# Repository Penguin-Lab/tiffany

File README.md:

# tiffany
A Tiffany é uma hexapod desenvolvida para andar de forma autônoma ou para ser controlada pelo celular. Para se locomover, ela possui 6 patas de 3 graus de liberdade cada (3 motores) e uma ESP32 que comanda o conjunto! Ela é a segunda integrante robótica do nosso espaço inteligente!

# Estrutura física
A estrutura física do robô é composta por seis patas de três eixos cada (três motores). As patas são fixadas a duas placas de PLA para deixar o robô firme. As peças são todas projetadas em 3D e foram impressas utilizando PLA, podendo ser encontradas na pasta Pecas_3d deste projeto.

## Peças 3D em STL
As peças em 3D desenvolvidas para este projeto foram baseadas no projeto do hexapod Steve da Eng. Eletricista Bruna Reis Lyra. Na pasta Pecas_3d, é possível encontrar duas versões dessas peças em STL: uma desenhada para o motor servo TowerPro MG995 (v1) e outra para o DS3230 (v2). Para ajudar, segue abaixo uma lista de todas as peças que devem ser impressas e qual o valor da sua maior dimensão (para ajudar na escolha da impressora):

### V1: Versão para o motor servo TowerPro MG995 
* Corpo
  * 1x [TIFFANY_BODY_DOWN.STL (230 mm)](https://github.com/Penguin-Lab/tiffany/blob/main/Pecas_3d/v1/TIFFANY_BODY_DOWN.STL)
  * 1x [TIFFANY_BODY_UP.STL (230 mm)](https://github.com/Penguin-Lab/tiffany/blob/main/Pecas_3d/v1/TIFFANY_BODY_UP.STL)
  * 6x [TIFFANY_SPACER.STL (68 mm)](https://github.com/Penguin-Lab/tiffany/blob/main/Pecas_3d/v1/TIFFANY_SPACER.STL)
  * 1x [TIFFANY_SUPPORT_PCI.STL (120 mm)](https://github.com/Penguin-Lab/tiffany/blob/main/Pecas_3d/v1/TIFFANY_SUPPORT_PCI.STL)
  * 1x [TIFFANY_SUPPORT_SWITCH.STL (50 mm)](https://github.com/Penguin-Lab/tiffany/blob/main/Pecas_3d/v1/TIFFANY_SUPPORT_SWITCH.STL)
* Patas
  * 6x [TIFFANY_TIBIA_LEFT.STL (141 mm)](https://github.com/Penguin-Lab/tiffany/blob/main/Pecas_3d/v1/TIFFANY_TIBIA_LEFT.STL)
  * 6x [TIFFANY_TIBIA_LEFT.STL espelhado (141 mm)](https://github.com/Penguin-Lab/tiffany/blob/main/Pecas_3d/v1/TIFFANY_TIBIA_LEFT.STL)
  * 6x [TIFFANY_TIBIA_MIDDLE.STL (63 mm)](https://github.com/Penguin-Lab/tiffany/blob/main/Pecas_3d/v1/TIFFANY_TIBIA_MIDDLE.STL)
  * 6x [TIFFANY_TIBIA_TUBO.STL (10 mm)](https://github.com/Penguin-Lab/tiffany/blob/main/Pecas_3d/v1/TIFFANY_TIBIA_TUBO.STL)
  * 6x [TIFFANY_FOOT.STL (25 mm)](https://github.com/Penguin-Lab/tiffany/blob/main/Pecas_3d/v1/TIFFANY_FOOT.STL)
  * 3x [TIFFANY_FEMUR_FRONT.STL (110 mm)](https://github.com/Penguin-Lab/tiffany/blob/main/Pecas_3d/v1/TIFFANY_FEMUR_FRONT.STL)
  * 3x [TIFFANY_FEMUR_BACK.STL (118 mm)](https://github.com/Penguin-Lab/tiffany/blob/main/Pecas_3d/v1/TIFFANY_FEMUR_BACK.STL)
  * 3x [TIFFANY_FEMUR_FRONT.STL espelhado (110 mm)](https://github.com/Penguin-Lab/tiffany/blob/main/Pecas_3d/v1/TIFFANY_FEMUR_FRONT.STL)
  * 3x [TIFFANY_FEMUR_BACK.STL espelhado (118 mm)](https://github.com/Penguin-Lab/tiffany/blob/main/Pecas_3d/v1/TIFFANY_FEMUR_BACK.STL)
  * 6x [TIFFANY_FEMUR_MIDDLE.STL (51 mm)](https://github.com/Penguin-Lab/tiffany/blob/main/Pecas_3d/v1/TIFFANY_FEMUR_MIDDLE.STL)
  * 6x [TIFFANY_OMBRO_UP.STL (61 mm)](https://github.com/Penguin-Lab/tiffany/blob/main/Pecas_3d/v1/TIFFANY_OMBRO_UP.STL)
  * 3x [TIFFANY_OMBRO_DOWN_LEFT.STL (61 mm)](https://github.com/Penguin-Lab/tiffany/blob/main/Pecas_3d/v1/TIFFANY_OMBRO_DOWN_LEFT.STL)
  * 3x [TIFFANY_OMBRO_DOWN_LEFT.STL espelhado (61 mm)](https://github.com/Penguin-Lab/tiffany/blob/main/Pecas_3d/v1/TIFFANY_OMBRO_DOWN_LEFT.STL)
* Motor
  * 12x [TIFFANY_TAMPA_MOTOR.STL (41 mm)](https://github.com/Penguin-Lab/tiffany/blob/main/Pecas_3d/v1/TIFFANY_TAMPA_MOTOR.STL)

Obs: a tampa de 12 motores deverão ser trocadas pelas peças [TIFFANY_TAMPA_MOTOR.STL](https://github.com/Penguin-Lab/tiffany/blob/main/Pecas_3d/v1/TIFFANY_TAMPA_MOTOR.STL) para que seja possível fixar os rolamentos nas patas. Serão utilizados 3 rolamentos por pata:

### V2: Versão para o motor servo DS3230 PRO-180 
* Corpo
  * 1x [TIFFANY_BODY_DOWN.STL (230 mm)](https://github.com/Penguin-Lab/tiffany/blob/main/Pecas_3d/v2/TIFFANY_BODY_DOWN.STL)
  * 1x [TIFFANY_BODY_UP.STL (230 mm)](https://github.com/Penguin-Lab/tiffany/blob/main/Pecas_3d/v2/TIFFANY_BODY_UP.STL)
  * 2x [TIFFANY_SPACER.STL (67 mm)](https://github.com/Penguin-Lab/tiffany/blob/main/Pecas_3d/v2/TIFFANY_SPACER.STL)
  * 4x [TIFFANY_SPACER_FRONT.STL (63 mm)](https://github.com/Penguin-Lab/tiffany/blob/main/Pecas_3d/v2/TIFFANY_SPACER_FRONT.STL)
  * 1x [TIFFANY_SUPORT_PCI.STL (120 mm)](https://github.com/Penguin-Lab/tiffany/blob/main/Pecas_3d/v2/TIFFANY_SUPORT_PCI.STL)
  * 1x [TIFFANY_SUPORT_SWITCH.STL (50 mm)](https://github.com/Penguin-Lab/tiffany/blob/main/Pecas_3d/v2/TIFFANY_SUPORT_SWITCH.STL)
  * 1x [TIFFANY_SUPORT_BATTERY_PLUG.STL (44 mm)](https://github.com/Penguin-Lab/tiffany/blob/main/Pecas_3d/v2/TIFFANY_SUPORT_BATTERY_PLUG.STL)
  * 1x [TIFFANY_LOGO.STL (36 mm)](https://github.com/Penguin-Lab/tiffany/blob/main/Pecas_3d/v2/TIFFANY_LOGO.STL)
* Patas
  * 6x [TIFFANY_TIBIA_LEFT.STL (141 mm)](https://github.com/Penguin-Lab/tiffany/blob/main/Pecas_3d/v2/TIFFANY_TIBIA_LEFT.STL)
  * 6x [TIFFANY_TIBIA_LEFT.STL espelhado (141 mm)](https://github.com/Penguin-Lab/tiffany/blob/main/Pecas_3d/v2/TIFFANY_TIBIA_LEFT.STL)
  * 6x [TIFFANY_TIBIA_MIDDLE.STL (63 mm)](https://github.com/Penguin-Lab/tiffany/blob/main/Pecas_3d/v2/TIFFANY_TIBIA_MIDDLE.STL)
  * 6x [TIFFANY_TIBIA_TUBO.STL (10 mm)](https://github.com/Penguin-Lab/tiffany/blob/main/Pecas_3d/v2/TIFFANY_TIBIA_TUBO.STL)
  * 6x [TIFFANY_FOOT.STL (25 mm)](https://github.com/Penguin-Lab/tiffany/blob/main/Pecas_3d/v2/TIFFANY_FOOT.STL)
  * 3x [TIFFANY_FEMUR_FRONT.STL (110 mm)](https://github.com/Penguin-Lab/tiffany/blob/main/Pecas_3d/v2/TIFFANY_FEMUR_FRONT.STL)
  * 3x [TIFFANY_FEMUR_BACK.STL (118 mm)](https://github.com/Penguin-Lab/tiffany/blob/main/Pecas_3d/v2/TIFFANY_FEMUR_BACK.STL)
  * 3x [TIFFANY_FEMUR_FRONT.STL espelhado (110 mm)](https://github.com/Penguin-Lab/tiffany/blob/main/Pecas_3d/v2/TIFFANY_FEMUR_FRONT.STL)
  * 3x [TIFFANY_FEMUR_BACK.STL espelhado (118 mm)](https://github.com/Penguin-Lab/tiffany/blob/main/Pecas_3d/v2/TIFFANY_FEMUR_BACK.STL)
  * 6x [TIFFANY_FEMUR_MIDDLE.STL (51 mm)](https://github.com/Penguin-Lab/tiffany/blob/main/Pecas_3d/v2/TIFFANY_FEMUR_MIDDLE.STL)
  * 6x [TIFFANY_OMBRO_UP.STL (61 mm)](https://github.com/Penguin-Lab/tiffany/blob/main/Pecas_3d/v2/TIFFANY_OMBRO_UP.STL)
  * 3x [TIFFANY_OMBRO_DOWN_LEFT.STL (61 mm)](https://github.com/Penguin-Lab/tiffany/blob/main/Pecas_3d/v2/TIFFANY_OMBRO_DOWN_LEFT.STL)
  * 3x [TIFFANY_OMBRO_DOWN_LEFT.STL espelhado (61 mm)](https://github.com/Penguin-Lab/tiffany/blob/main/Pecas_3d/v2/TIFFANY_OMBRO_DOWN_LEFT.STL)
* Motor
  * 12x [TIFFANY_TAMPA_MOTOR_DS3230.STL (41 mm)](https://github.com/Penguin-Lab/tiffany/blob/main/Pecas_3d/v2/TIFFANY_TAMPA_MOTOR_DS3230.STL)

Obs: no caso do DS3230, a tampa de 12 motores deverão ser trocadas pelas peças [TIFFANY_TAMPA_MOTOR_DS3230.STL](https://github.com/Penguin-Lab/tiffany/blob/main/Pecas_3d/v2/TIFFANY_TAMPA_MOTOR_DS3230.STL) para que seja possível fixar os rolamentos nas patas. Serão utilizados 3 rolamentos por pata.

## Outros itens da estrutura
Alguns outros itens são necessários para finalizar a estrutura da Tiffany:
* 6x Parafusos m4 ou similar de cm: prender as peças [TIFFANY_BODY_UP.STL](https://github.com/Penguin-Lab/tiffany/blob/main/Pecas_3d/TIFFANY_BODY_UP.STL) e [TIFFANY_BODY_DOWN.STL](https://github.com/Penguin-Lab/tiffany/blob/main/Pecas_3d/TIFFANY_BODY_DOWN.STL)
* 24x Parafusos m4 de cm: prender as peças [TIFFANY_OMBRO_DOWN_LEFT.STL](https://github.com/Penguin-Lab/tiffany/blob/main/Pecas_3d/TIFFANY_OMBRO_DOWN_LEFT.STL) e [TIFFANY_OMBRO_UP.STL](https://github.com/Penguin-Lab/tiffany/blob/main/Pecas_3d/TIFFANY_OMBRO_UP.STL)
* 24x Parafusos m3 de cm: prender as peças [TIFFANY_TIBIA_LEFT.STL](https://github.com/Penguin-Lab/tiffany/blob/main/Pecas_3d/TIFFANY_TIBIA_LEFT.STL) nos motores
* 6x Tiras de EVA: colocar na ponta das peças [TIFFANY_FOOT.STL](https://github.com/Penguin-Lab/tiffany/blob/main/Pecas_3d/TIFFANY_FOOT.STL) para evitar que o robô deslize
* Arruelas entre as peças [TIFFANY_SPACER.STL](https://github.com/Penguin-Lab/tiffany/blob/main/Pecas_3d/TIFFANY_SPACER.STL) e [TIFFANY_BODY_UP.STL](https://github.com/Penguin-Lab/tiffany/blob/main/Pecas_3d/TIFFANY_BODY_UP.STL) para ajustar a altura correta do interior do robô

## Placa de circuito impresso
No projeto, foi desenvolvida uma placa de circuito para servir como shield para a ESP32 e conexão com as duas placas PCA9685.

## Calibração dos motores
A calibração dos motores é feita utilizando o [CALIBRADOR DE MOTORES](https://github.com/Penguin-Lab/calib_servomotor) conectado às PCAs da Tiffany. Isso deve ser feito pelo clock das PCAs ser diferente de uma placa para outra. Logo, os motores da esquerda são calibrados utilizando a PCA da esquerda e os da direita com a PCA da direita. Os valores retornados pela calibração são jogados nesta [PLANILHA](https://docs.google.com/spreadsheets/d/1Kh9AVbb79lXnJq5dlCiB7NEVVmcJWRX6X2CdDR9_QZo/edit?usp=sharing). A planilha ajeita os valores de PWM retornados na IDE do Arduino para valores que representem 0 e 180 graus dos motores já na estrutura das patas. Esses valores são os mesmos listados no código de comando da Tiffany.

## Componentes eletrônicos
Os componentes eletrônicos embarcados no robô e equipamentos utilizados estão listados abaixo.
### V1: Versão para o motor servo TowerPro MG995 
* Controlador com Wi-fi e Bluetooth
  * 1x ESP32 (38 pinos)
* Motores
  * 18x Servo TowerPro MG995 Metálico
* 2x Placas PCA9685 para comando dos 18 motores (9 motores em cada)
* Chave (switch)
* Alimentação
  * Bateria Zippy LiFe 1100mAh 2s 6,6V (ESP32)
  * Bateria TM Hobbies LiFe 2100mAh 2s 6,6v (motores)

### V2: Versão para o motor servo DS3230 PRO-180 
* Controlador com Wi-fi e Bluetooth
  * 1x ESP32 (38 pinos)
* Motores
  * 18x Servo DS3230 PRO-180
* 2x Placas PCA9685 para comando dos 18 motores (9 motores em cada)
* Chave (switch)
* Chave pequena (switch)
* Alimentação
  * Regulador para 5V (ESP32)
  * Regulador HV SBEC YPG 20A configurado para saída de 6V (motores)
  * Bateria LiPo 5000mAh 3s 11,1V (motores)

# Software
Na pasta de códigos, há dois códigos de programação da ESP32 (38 pinos). Eles são exemplos em C++ do comando de movimentação da Tiffany:
* Dabble: a ESP32 pode se comunicar com o aplicativo Dabble no celular e receber comandos de ação;
* Espaço Inteligente (IS): a ESP32 pode se comunicar com o Espaço Inteligente e receber esses mesmos comandos.

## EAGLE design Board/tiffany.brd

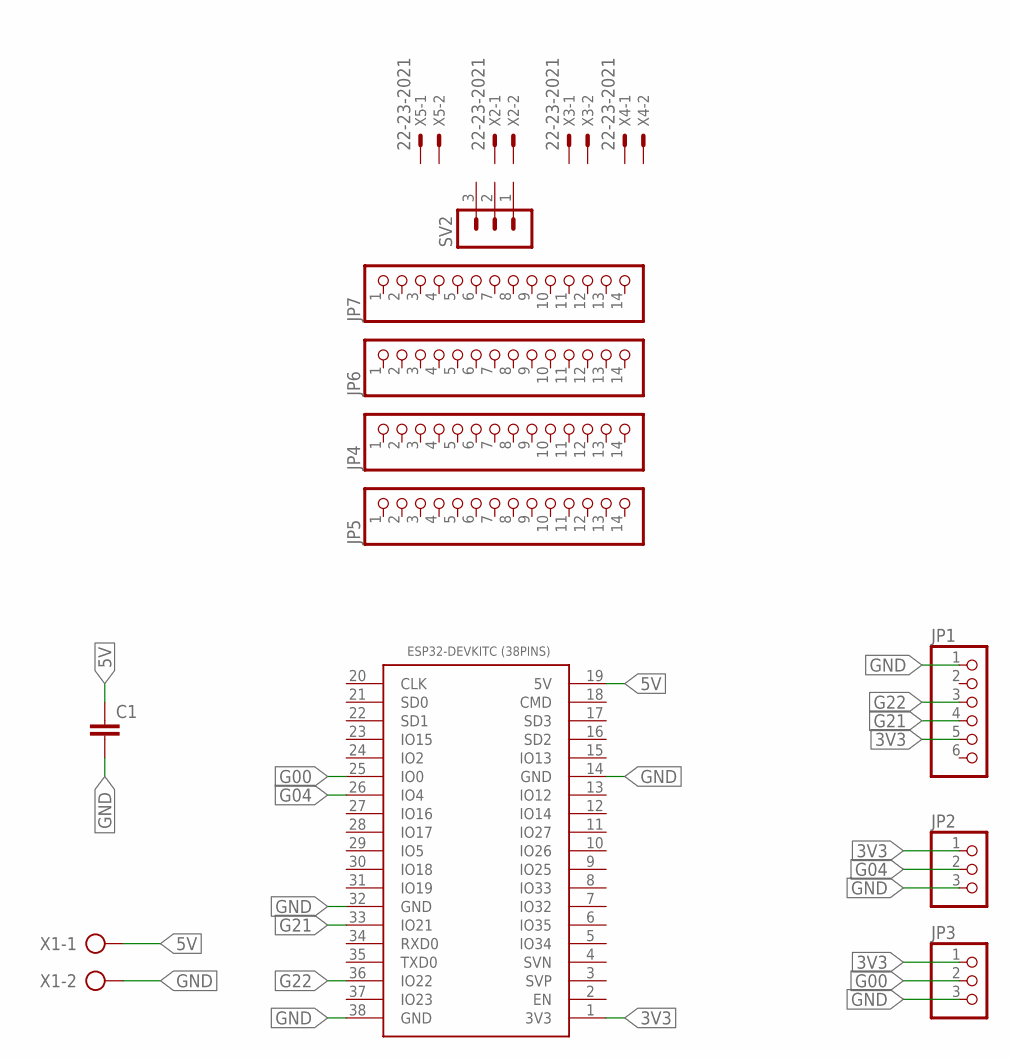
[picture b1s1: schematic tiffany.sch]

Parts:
C1: C-EU050-024X044; C050-024X044
ESP32-DEVKITC(38PINS)1: ESP32DEVKITC_38PINS; ESP32-DEVKITC
JP1: PINHD-1X6; 1X06
JP2, JP3: PINHD-1X3; 1X03
JP4, JP5, JP6, JP7: PINHD-1X14; 1X14
SV2: MA03-1
X1: AK300/2
X2, X3, X4, X5: 22-23-2021

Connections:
3V3: ESP32-DEVKITC(38PINS)1.1 (3V3), JP1.5, JP2.1, JP3.1
5V: C1.1, ESP32-DEVKITC(38PINS)1.19 (5V), X1.1
G00: ESP32-DEVKITC(38PINS)1.25 (IO0), JP3.2
G04: ESP32-DEVKITC(38PINS)1.26 (IO4), JP2.2
G21: ESP32-DEVKITC(38PINS)1.33 (IO21), JP1.4
G22: ESP32-DEVKITC(38PINS)1.36 (IO22), JP1.3
GND: C1.2, ESP32-DEVKITC(38PINS)1.14 (GND), ESP32-DEVKITC(38PINS)1.32 (GND), ESP32-DEVKITC(38PINS)1.38 (GND), JP1.1, JP2.3, JP3.3, X1.2

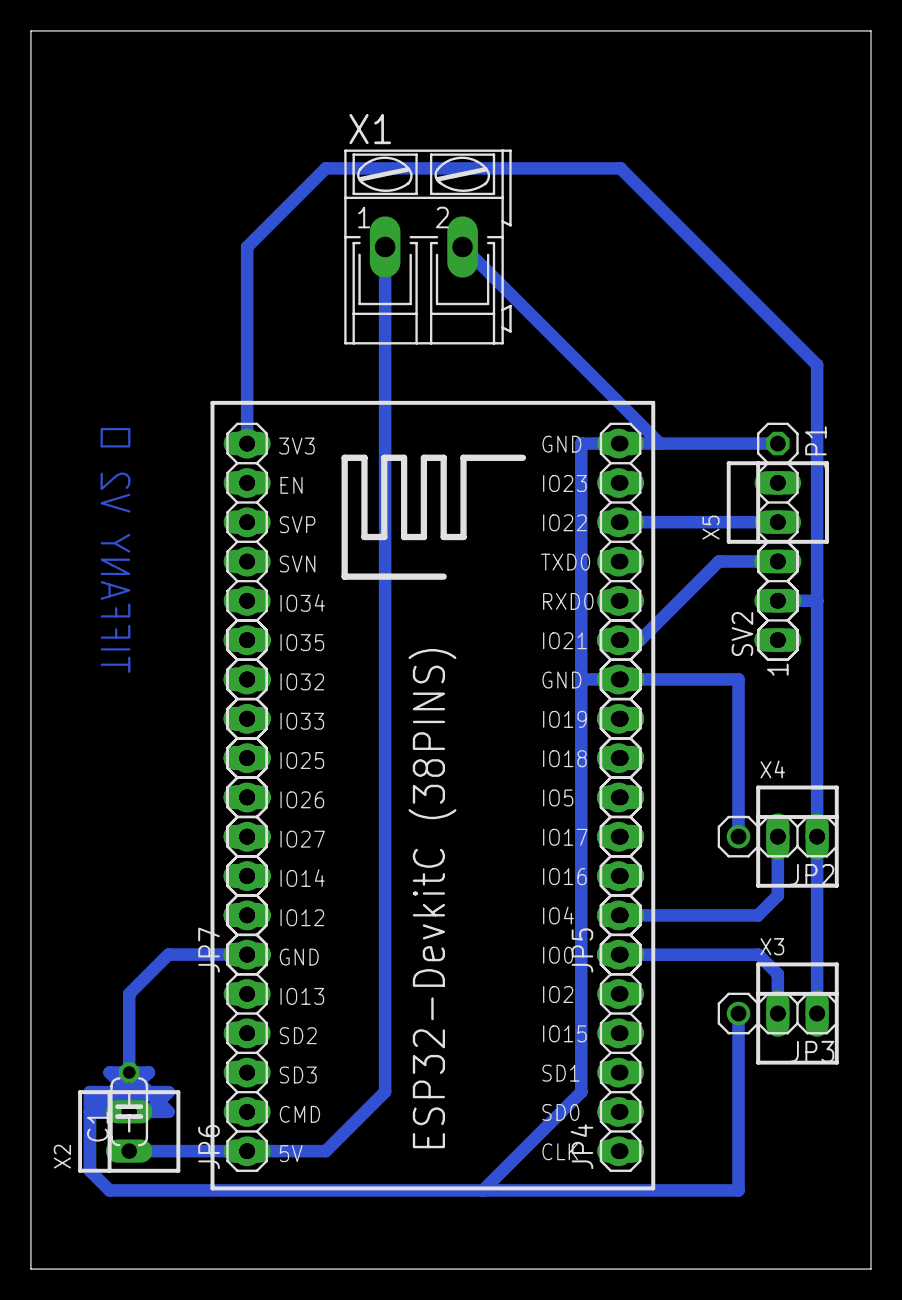
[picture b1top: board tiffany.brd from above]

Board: 2 copper layers, 54.3 x 80.0 mm, 15 parts (0 on the bottom side), 7 nets.

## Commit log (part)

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2021-12-20 Add files via upload
    fotos da tiffany
2021-12-20 Create images
2021-12-20 Create test
2021-12-20 Add files via upload
    fotos tiffany
2021-12-20 Update README.md
    explicação sobre as peças 3d
2021-12-20 Add files via upload
    Peças 3d em STL
2021-12-20 Add files via upload
    vista explodida da pata
2022-05-20 código de controle de movimento da Tiffany
    Código de comando de andar pra frente, andar pra trás e girar no seu próprio eixo
2022-05-20 placa_de_alimentacao
2022-05-20 shield da esp dummy
2022-08-23 código de controle de movimento (otimizado)
    Código de andar pra frente, pra trás, girar e dançar. Utilizando uma biblioteca autoral.
2022-08-23 Arquivos utilizados
    Arquivos utilizados para elaboração do Hexapod Tiffany
2025-04-30 Update 30/04/2025
    Adicionado mover inclinado
2025-04-30 Update 30/04/2025
    Alterado para gerar a trajetória enquanto anda.
2025-04-30 Update 30/04/2025
    Adicionado movimento omnidirecional com analógico
2025-05-01 Update 01/05/2025
    Adicionada a função de girar no próprio eixo ou enquanto anda. Ainda não testada
2025-05-01 Update 01/05/2025b
    Mudei os offsets do ripple gait. Ainda não testado.
2025-05-01 Update 01/05/2025c
    Adicionei mais uma forma de ripple. Tenho que testar as duas
2025-05-02 Update 02/05/2025
    Adicionado o mover pata para uma posição específica. No exemplo, 10cm pra frente e 10cm pra cima (tipo subir um degrau).
2025-05-05 Rename tiffany_board_v2.pdf to Board/tiffany_board_v2.pdf
2025-10-24 Rename Pecas_3d/MONTAGEM.STL to Pecas_3d/v1/MONTAGEM.STL
2025-10-24 Rename Pecas_3d/TIFFANY_BODY_DOWN.STL to Pecas_3d/v1/TIFFANY_BODY_DOWN.STL
2025-10-24 Rename Pecas_3d/TIFFANY_BODY_UP.STL to Pecas_3d/v1/TIFFANY_BODY_UP.STL
2025-10-24 Rename Pecas_3d/TIFFANY_FEMUR_BACK.STL to Pecas_3d/v1/TIFFANY_FEMUR_BACK.STL
2025-10-24 Rename Pecas_3d/TIFFANY_FEMUR_FRONT.STL to Pecas_3d/v1/TIFFANY_FEMUR_FRONT.STL
2025-10-24 Rename Pecas_3d/TIFFANY_FEMUR_MIDDLE.STL to Pecas_3d/v1/TIFFANY_FEMUR_MIDDLE.STL
2025-10-24 Rename Pecas_3d/TIFFANY_FOOT.STL to Pecas_3d/v1/TIFFANY_FOOT.STL
2025-10-24 Rename Pecas_3d/TIFFANY_OMBRO_DOWN_LEFT.STL to Pecas_3d/v1/TIFFANY_OMBRO_DOWN_LEFT.STL
2025-10-24 Rename Pecas_3d/TIFFANY_OMBRO_UP.STL to Pecas_3d/v1/TIFFANY_OMBRO_UP.STL
2025-10-24 Rename Pecas_3d/TIFFANY_SPACER.STL to Pecas_3d/v1/TIFFANY_SPACER.STL
2025-10-24 Rename Pecas_3d/TIFFANY_SUPPORT_PCI.STL to Pecas_3d/v1/TIFFANY_SUPPORT_PCI.STL
2025-10-24 Rename Pecas_3d/TIFFANY_SUPPORT_SWITCH.STL to Pecas_3d/v1/TIFFANY_SUPPORT_SWITCH.STL
2025-10-24 Rename Pecas_3d/TIFFANY_TAMPA_MOTOR.STL to Pecas_3d/v1/TIFFANY_TAMPA_MOTOR.STL
2025-10-24 Rename Pecas_3d/TIFFANY_TIBIA_LEFT.STL to Pecas_3d/v1/TIFFANY_TIBIA_LEFT.STL
2025-10-24 Rename Pecas_3d/TIFFANY_TIBIA_MIDDLE.STL to Pecas_3d/v1/TIFFANY_TIBIA_MIDDLE.STL
2025-10-24 Rename Pecas_3d/TIFFANY_TIBIA_TUBO.STL to Pecas_3d/v1/TIFFANY_TIBIA_TUBO.STL
2025-10-24 Rename Pecas_3d/TIFFANY_BODY_DOWN.STL to Pecas_3d/v2/TIFFANY_BODY_DOWN.STL
2025-11-04 Update fmt.Println message from 'Hello' to 'Goodbye'
2025-11-05 Change device name from 'Scarlet' to 'Tiffany'
2025-11-06 Rename TIFFANY_SUPPORT_PCI.STL to TIFFANY_SUPORT_PCI.STL
2025-11-07 Refactor joystick angle calculations and delays
    Refactor joystickToRad function and add overload with deltaAngle. Update delay values and adjust angles for hexapod movement.
2025-11-07 Add motor calibration section to README
    Added a section on motor calibration using the CALIBRADOR DE MOTORES, detailing the calibration process and linking to relevant resources.
2025-11-10 Refactor joystick angle functions for clarity
2025-11-10 Rename Codes/tiffany_v2/tiffany_v2.ino to Codes/v1/tiffany_v1/tiffany_v1.ino
2025-11-10 Rename Codes/tiffany_v2_IS/tiffany_v2_IS.ino to Codes/v1/tiffany_v1_IS/tiffany_v1_IS.ino
2025-11-10 Rename Codes/tiffany_v2_IS/tiffany_command_IS.py to Codes/v1/tiffany_v1_IS/tiffany_command_IS.py
2025-11-10 Add new version of tiffany sketch
2025-11-10 Update print statement from 'Hello' to 'Goodbye'
2025-11-10 Add basic Pygame control and messaging functionality
2025-11-12 Refactor joystick control logic for clarity
2025-12-01 Update leg parameters for hexapod configuration
2026-03-11 Adjust angle thresholds and joystick sensitivity
2026-06-08 Integrate BNO08x IMU and modify debug flag
    Added BNO08x IMU support and updated debug settings.
